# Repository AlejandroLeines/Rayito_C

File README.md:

# Rayito_C
En este repositorio se encuentra el codigo de Rayito en lengiaje C

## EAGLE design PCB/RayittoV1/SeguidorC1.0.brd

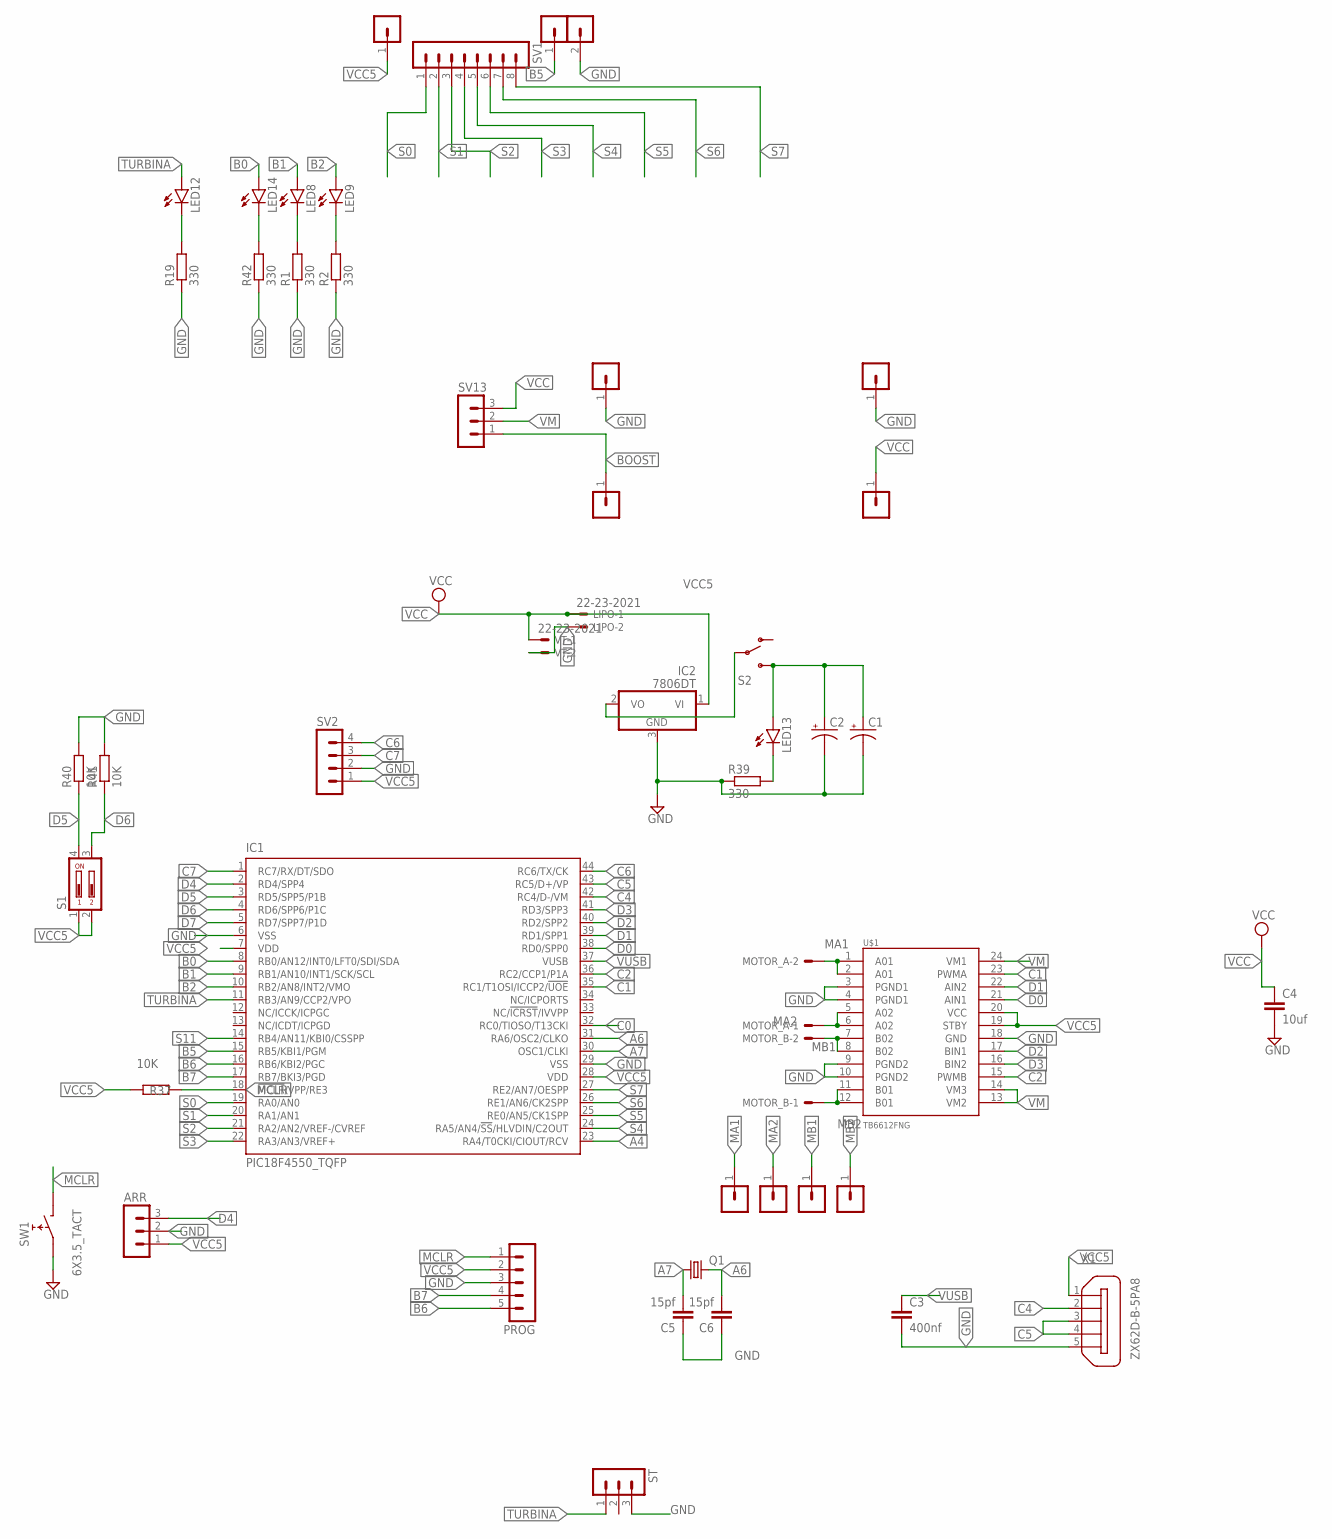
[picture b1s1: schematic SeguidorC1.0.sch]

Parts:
ARR: MA03-1
C1, C2: CPOL-US153CLV-0505; 153CLV-0505
C3: 400nf; C0805
C4: 10uf; C0805
C5, C6: 15pf; C0805
IC1: PIC18F4550_TQFP; TQFP44
IC2: 7806DT; TO252
LED8, LED9, LED12, LED13, LED14: LEDCHIP-LED0805; CHIP-LED0805
LIPO: 22-23-2021
MOTOR_A: 22-23-2021
MOTOR_B: 22-23-2021
PROG: MA05-1
Q1: CRYSTALHC49U-V; HC49U-V
R1, R2, R19, R39, R42: 330; R0805
R37, R40, R41: 10K; R0805
S1: DIP02YL
S2: SWITCH-SPSTPTH; SWITCH-SPDT
ST: MA03-1
SV1: MA08-1
SV2: MA04-1
SV3, SV4, SV5, SV6, SV7, SV9, SV10, SV11, SV12: MA01-1
SV8: MA02-1
SV13: MA03-1
SW1: 6X3.5_TACT; TACT_6X3.5
U$1: TB6612FNG; SSOP24
VT: 22-23-2021
X1: ZX62D-B-5PA8

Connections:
A4: IC1.23 (RA4/T0CKI/CIOUT/RCV)
A6: C6.2, IC1.31 (RA6/OSC2/CLKO), Q1.2
A7: C5.2, IC1.30 (OSC1/CLKI), Q1.1
B0: IC1.8 (RB0/AN12/INT0/LFT0/SDI/SDA), LED14.A
B1: IC1.9 (RB1/AN10/INT1/SCK/SCL), LED8.A
B2: IC1.10 (RB2/AN8/INT2/VMO), LED9.A
B5: IC1.15 (RB5/KBI1/PGM), SV8.1
B6: IC1.16 (RB6/KBI2/PGC), PROG.5
B7: IC1.17 (RB7/BKI3/PGD), PROG.4
BOOST: SV11.1, SV13.1
C0: IC1.32 (RC0/TIOSO/T13CKI)
C1: IC1.35 (RC1/T1OSI/ICCP2/!UOE), U$1.23 (PWMA)
C2: IC1.36 (RC2/CCP1/P1A), U$1.15 (PWMB)
C4: IC1.42 (RC4/D-/VM), X1.2
C5: IC1.43 (RC5/D+/VP), X1.3, X1.4
C6: IC1.44 (RC6/TX/CK), SV2.4
C7: IC1.1 (RC7/RX/DT/SDO), SV2.3
D0: IC1.38 (RD0/SPP0), U$1.21 (AIN1)
D1: IC1.39 (RD1/SPP1), U$1.22 (AIN2)
D2: IC1.40 (RD2/SPP2), U$1.17 (BIN1)
D3: IC1.41 (RD3/SPP3), U$1.16 (BIN2)
D4: ARR.3, IC1.2 (RD4/SPP4)
D5: IC1.3 (RD5/SPP5/P1B), R40.1, S1.4
D6: IC1.4 (RD6/SPP6/P1C), R41.1, S1.3
D7: IC1.5 (RD7/SPP7/P1D)
GND: ARR.2, C1.-, C2.-, C3.2, C4.2, C5.1, C6.1, IC1.6 (VSS), IC1.29 (VSS), IC2.3 (GND), LIPO.2, PROG.3, R1.1, R2.1, R19.1, R39.1, R40.2, R41.2, R42.1, ST.3, SV2.2, SV8.2 (3), SV9.1, SV10.1, SW1.P$1 (1), U$1.3 (PGND1), U$1.4 (PGND1), U$1.9 (PGND2), U$1.10 (PGND2), U$1.18 (GND), VT.2, X1.5
MA1: MOTOR_A.2, SV3.1, U$1.1 (A01), U$1.2 (A01)
MA2: MOTOR_A.1, SV4.1, U$1.5 (A02), U$1.6 (A02)
MB1: MOTOR_B.2, SV5.1, U$1.7 (B02), U$1.8 (B02)
MB2: MOTOR_B.1, SV6.1, U$1.11 (B01), U$1.12 (B01)
MCLR: IC1.18 (!MCLR!/VPP/RE3), PROG.1, R37.2, SW1.P$2 (2)
unnamed: IC2.2 (VO), S2.2
unnamed: LED8.C, R1.2
unnamed: LED9.C, R2.2
unnamed: LED12.C, R19.2
unnamed: LED13.C, R39.2
unnamed: LED14.C, R42.2
S0: IC1.19 (RA0/AN0), SV1.1
S1: IC1.20 (RA1/AN1), SV1.2
S2: IC1.21 (RA2/AN2/VREF-/CVREF), SV1.3
S3: IC1.22 (RA3/AN3/VREF+), SV1.4
S4: IC1.24 (RA5/AN4/!SS!/HLVDIN/C2OUT), SV1.5
S5: IC1.25 (RE0/AN5/CK1SPP), SV1.6
S6: IC1.26 (RE1/AN6/CK2SPP), SV1.7
S7: IC1.27 (RE2/AN7/OESPP), SV1.8
S11: IC1.14 (RB4/AN11/KBI0/CSSPP)
TURBINA: IC1.11 (RB3/AN9/CCP2/VPO), LED12.A, ST.1
VCC: C4.1, IC2.1 (VI), LIPO.1, SV12.1, SV13.3, VT.1
VCC5: ARR.1, C1.+, C2.+, IC1.7 (VDD), IC1.28 (VDD), LED13.A, PROG.2, R37.1, S1.1, S1.2, S2.3 (S), SV2.1, SV7.1, U$1.19 (STBY), U$1.20 (VCC), X1.1
VM: SV13.2, U$1.13 (VM2), U$1.14 (VM3), U$1.24 (VM1)
VUSB: C3.1, IC1.37 (VUSB)

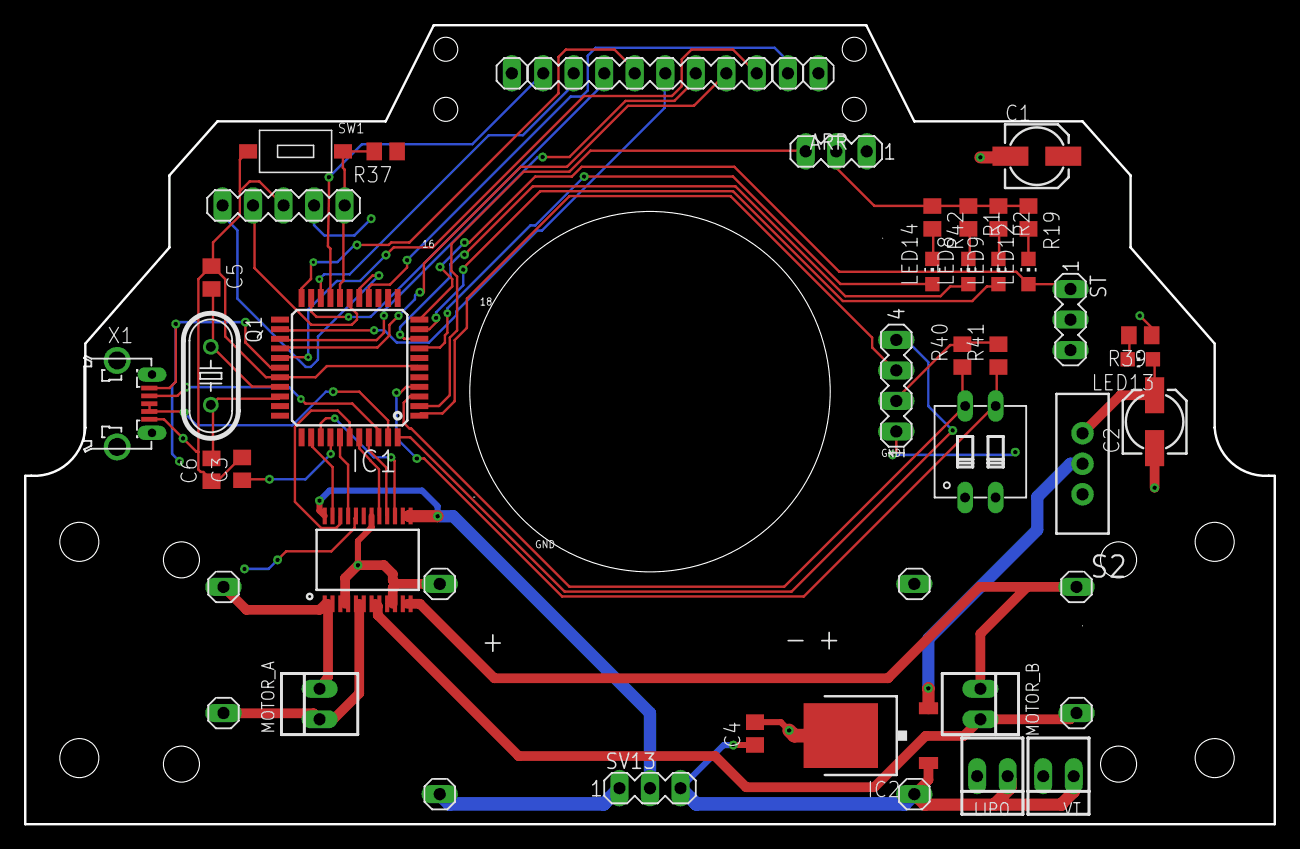
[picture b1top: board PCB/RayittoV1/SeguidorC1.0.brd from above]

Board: 2 copper layers, 104.0 x 66.5 mm, 47 parts (0 on the bottom side), 47 nets.

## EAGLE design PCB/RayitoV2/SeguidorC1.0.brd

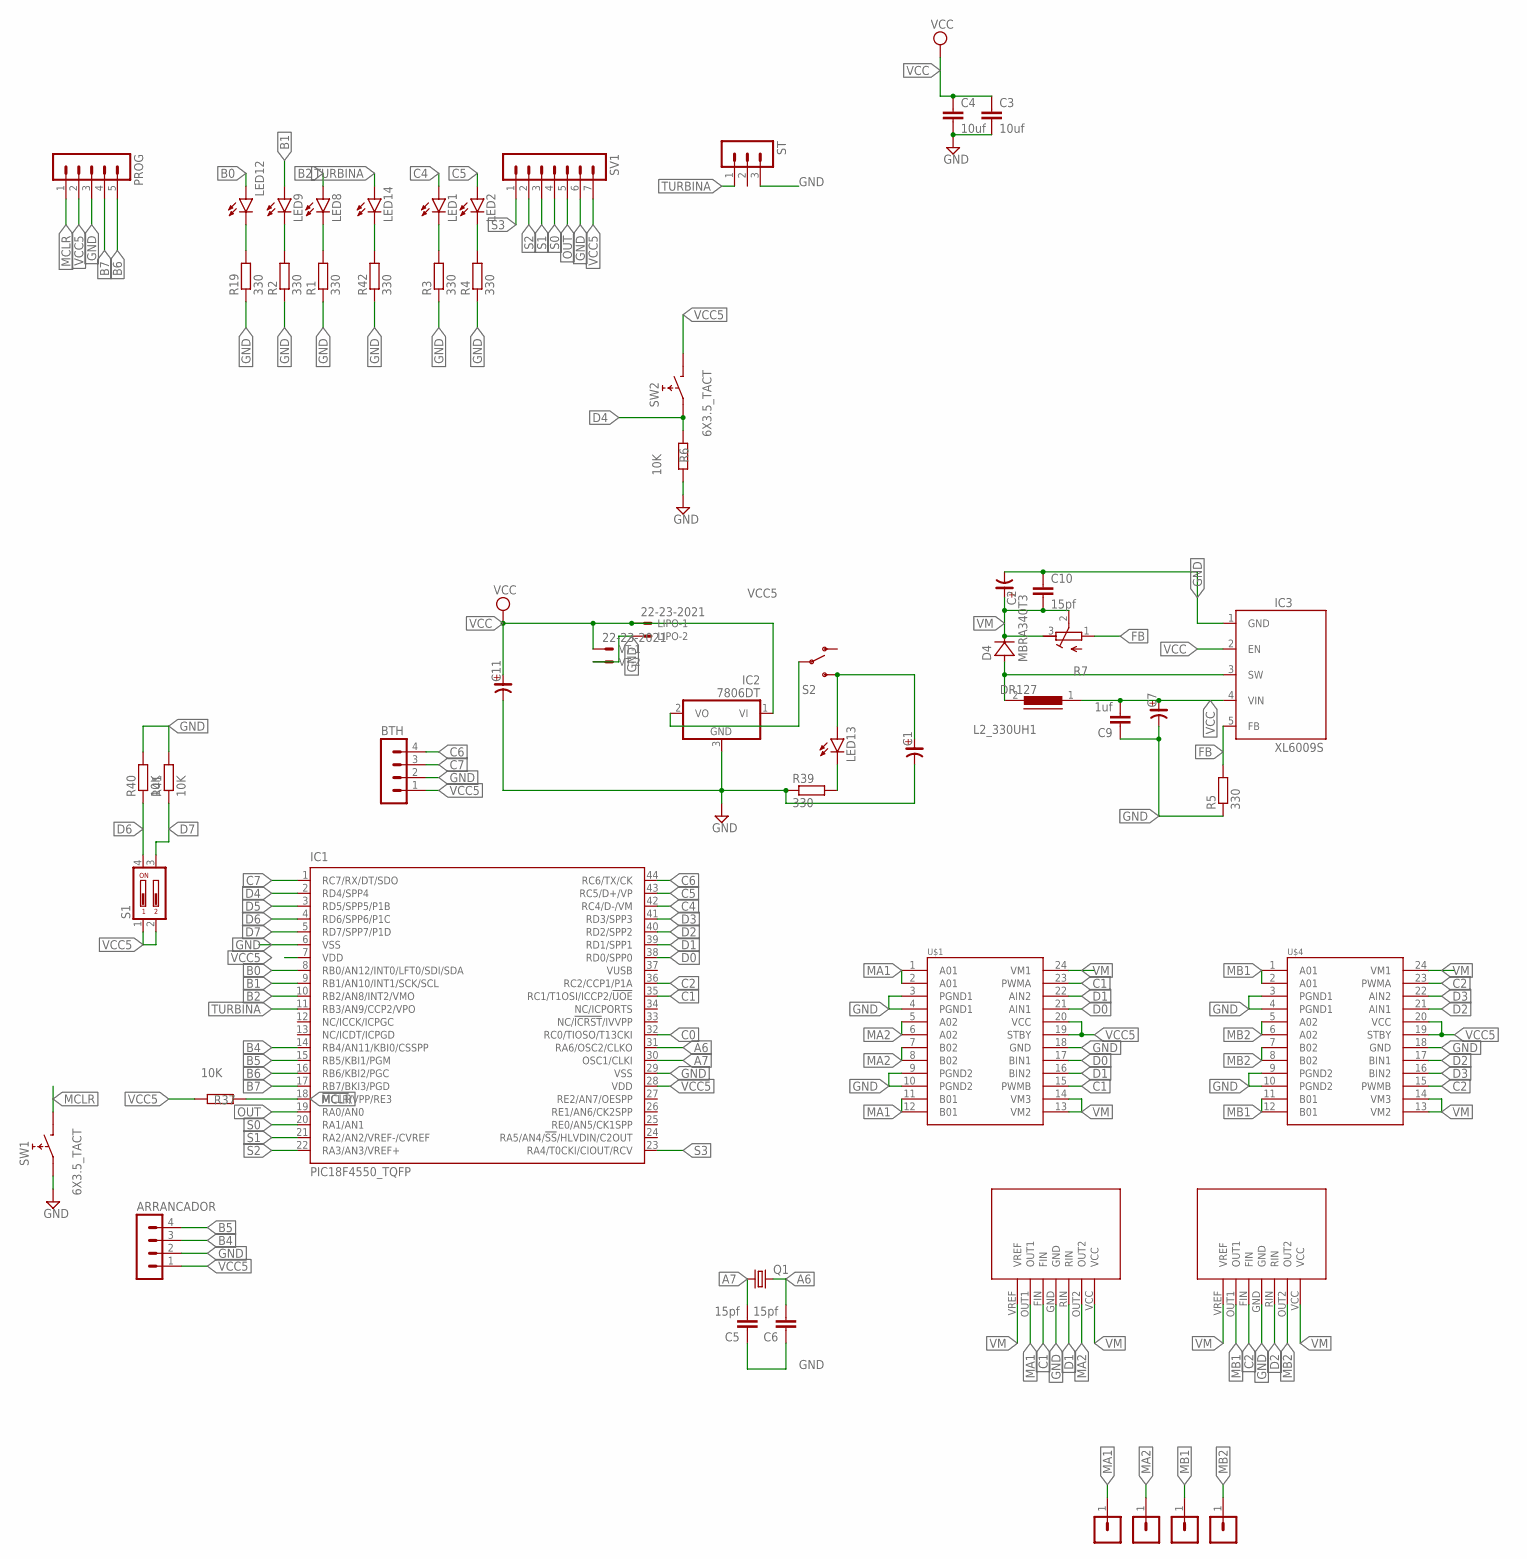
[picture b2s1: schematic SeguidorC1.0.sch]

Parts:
ARRANCADOR: MA04-1
BTH: MA04-1
C1, C2, C7, C11: CP_SV-D; CSV-D
C3, C4: 10uf; C0805
C5, C6, C10: 15pf; C0805
C9: 1uf; C0805
D4: MBRA340T3; SMA
IC1: PIC18F4550_TQFP; TQFP44
IC2: 7806DT; TO252
IC3: XL6009S; TO263-5
L2_330UH1: DR127
LED1, LED2, LED8, LED9, LED12, LED13, LED14: LEDCHIP-LED0805; CHIP-LED0805
LIPO: 22-23-2021
PROG: MA05-1
Q1: CRYSTALHC49U-V; HC49U-V
R1, R2, R3, R4, R5, R19, R39, R42: 330; R0805
R6, R37, R40, R41: 10K; R0805W
R7: R-TRIMM3296W; RTRIM3296W
S1: DIP02YL
S2: SWITCH-SPSTPTH; SWITCH-SPDT
ST: MA03-1
SV1: MA07-1
SV3, SV4, SV5, SV6: MA01-1
SW1, SW2: 6X3.5_TACT; TACT_6X3.5
U$1, U$4: TB6621FNG; SSOP24
U$2, U$3: BD623XXX; HRP7
VT: 22-23-2021

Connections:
A6: C6.2, IC1.31 (RA6/OSC2/CLKO), Q1.2
A7: C5.2, IC1.30 (OSC1/CLKI), Q1.1
B0: IC1.8 (RB0/AN12/INT0/LFT0/SDI/SDA), LED12.A
B1: IC1.9 (RB1/AN10/INT1/SCK/SCL), LED9.A
B2: IC1.10 (RB2/AN8/INT2/VMO), LED8.A
B4: ARRANCADOR.3, IC1.14 (RB4/AN11/KBI0/CSSPP)
B5: ARRANCADOR.4, IC1.15 (RB5/KBI1/PGM)
B6: IC1.16 (RB6/KBI2/PGC), PROG.5
B7: IC1.17 (RB7/BKI3/PGD), PROG.4
C0: IC1.32 (RC0/TIOSO/T13CKI)
C1: IC1.35 (RC1/T1OSI/ICCP2/!UOE), U$1.15 (PWMB), U$1.23 (PWMA), U$2.FIN
C2: IC1.36 (RC2/CCP1/P1A), U$3.FIN, U$4.15 (PWMB), U$4.23 (PWMA)
C4: IC1.42 (RC4/D-/VM), LED1.A
C5: IC1.43 (RC5/D+/VP), LED2.A
C6: BTH.4, IC1.44 (RC6/TX/CK)
C7: BTH.3, IC1.1 (RC7/RX/DT/SDO)
D0: IC1.38 (RD0/SPP0), U$1.17 (BIN1), U$1.21 (AIN1)
D1: IC1.39 (RD1/SPP1), U$1.16 (BIN2), U$1.22 (AIN2), U$2.RIN
D2: IC1.40 (RD2/SPP2), U$3.RIN, U$4.17 (BIN1), U$4.21 (AIN1)
D3: IC1.41 (RD3/SPP3), U$4.16 (BIN2), U$4.22 (AIN2)
D4: IC1.2 (RD4/SPP4), R6.2, SW2.P$1 (1)
D5: IC1.3 (RD5/SPP5/P1B)
D6: IC1.4 (RD6/SPP6/P1C), R40.1, S1.4
D7: IC1.5 (RD7/SPP7/P1D), R41.1, S1.3
FB: IC3.5 (FB), R5.2, R7.1 (A)
GND: ARRANCADOR.2, BTH.2, C1.-, C2.-, C3.2, C4.2, C5.1, C6.1, C7.-, C9.1, C10.1, C11.-, IC1.6 (VSS), IC1.29 (VSS), IC2.3 (GND), IC3.1 (GND), LIPO.2, PROG.3, R1.1, R2.1, R3.1, R4.1, R5.1, R6.1, R19.1, R39.1, R40.2, R41.2, R42.1, ST.3, SV1.6, SW1.P$1 (1), U$1.3 (PGND1), U$1.4 (PGND1), U$1.9 (PGND2), U$1.10 (PGND2), U$1.18 (GND), U$2.GND, U$3.GND, U$4.3 (PGND1), U$4.4 (PGND1), U$4.9 (PGND2), U$4.10 (PGND2), U$4.18 (GND), VT.2
MA1: SV3.1, U$1.1 (A01), U$1.2 (A01), U$1.11 (B01), U$1.12 (B01), U$2.OUT1
MA2: SV4.1, U$1.5 (A02), U$1.6 (A02), U$1.7 (B02), U$1.8 (B02), U$2.OUT2
MB1: SV5.1, U$3.OUT1, U$4.1 (A01), U$4.2 (A01), U$4.11 (B01), U$4.12 (B01)
MB2: SV6.1, U$3.OUT2, U$4.5 (A02), U$4.6 (A02), U$4.7 (B02), U$4.8 (B02)
MCLR: IC1.18 (!MCLR!/VPP/RE3), PROG.1, R37.2, SW1.P$2 (2)
unnamed: IC2.2 (VO), S2.2
unnamed: LED8.C, R1.2
unnamed: LED9.C, R2.2
unnamed: LED1.C, R3.2
unnamed: LED2.C, R4.2
unnamed: D4.A, IC3.3 (SW), L2_330UH1.2
unnamed: LED12.C, R19.2
unnamed: LED13.C, R39.2
unnamed: LED14.C, R42.2
OUT: IC1.19 (RA0/AN0), SV1.5
S0: IC1.20 (RA1/AN1), SV1.4
S1: IC1.21 (RA2/AN2/VREF-/CVREF), SV1.3
S2: IC1.22 (RA3/AN3/VREF+), SV1.2
S3: IC1.23 (RA4/T0CKI/CIOUT/RCV), SV1.1
TURBINA: IC1.11 (RB3/AN9/CCP2/VPO), LED14.A, ST.1
VCC: C3.1, C4.1, C7.+, C9.2, C11.+, IC2.1 (VI), IC3.2 (EN), IC3.4 (VIN), L2_330UH1.1, LIPO.1, VT.1
VCC5: ARRANCADOR.1, BTH.1, C1.+, IC1.7 (VDD), IC1.28 (VDD), LED13.A, PROG.2, R37.1, S1.1, S1.2, S2.3 (S), SV1.7, SW2.P$2 (2), U$1.19 (STBY), U$1.20 (VCC), U$4.19 (STBY), U$4.20 (VCC)
VM: C2.+, C10.2, D4.C, R7.2 (S), R7.3 (E), U$1.13 (VM2), U$1.14 (VM3), U$1.24 (VM1), U$2.VCC, U$2.VREF, U$3.VCC, U$3.VREF, U$4.13 (VM2), U$4.14 (VM3), U$4.24 (VM1)

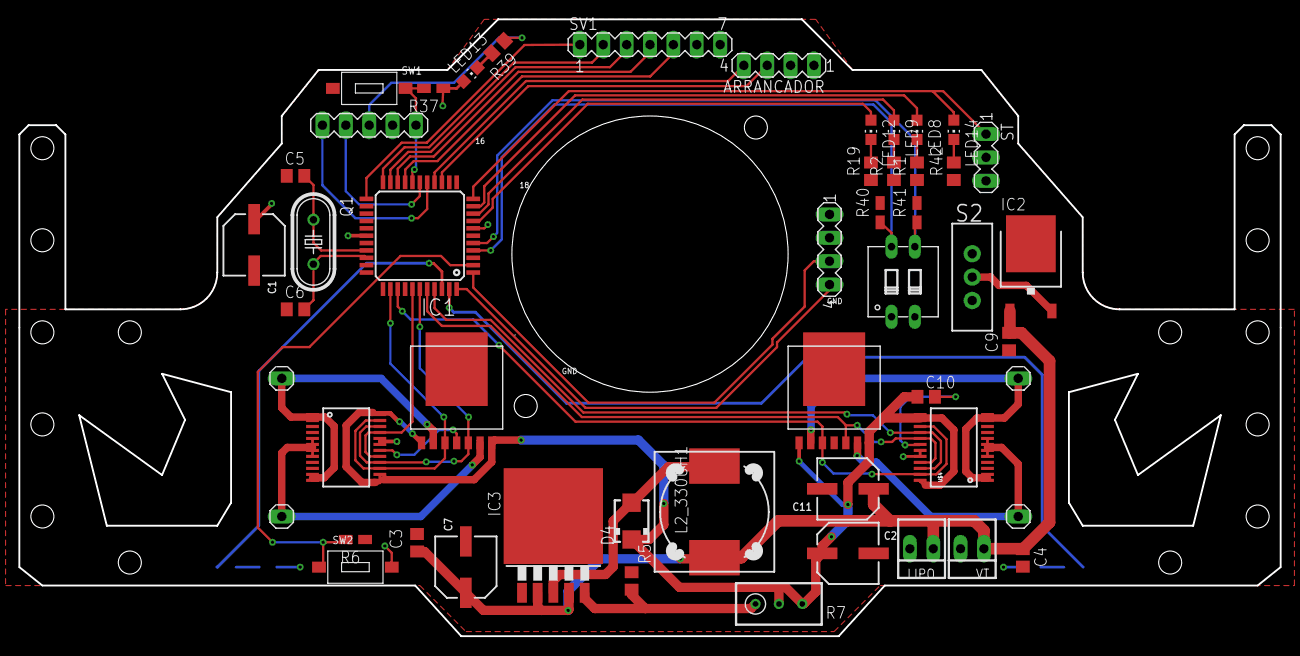
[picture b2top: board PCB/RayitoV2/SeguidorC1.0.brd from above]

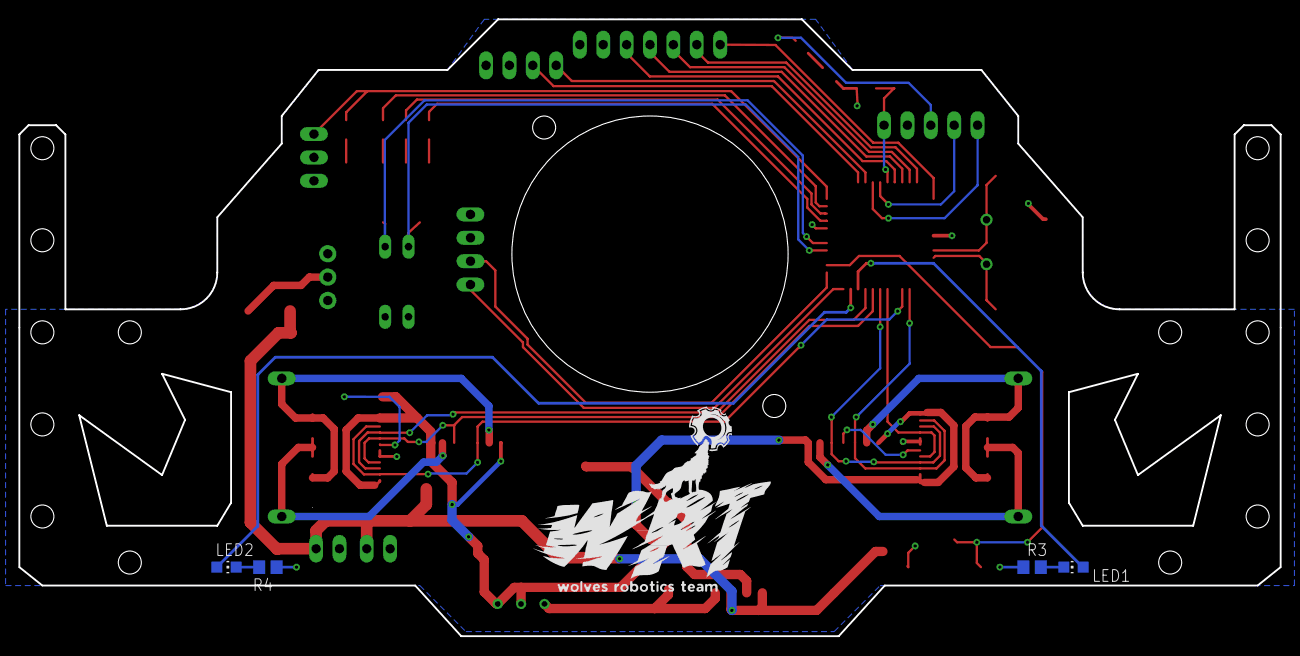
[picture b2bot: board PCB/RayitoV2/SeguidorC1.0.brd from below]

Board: 2 copper layers, 137.0 x 67.0 mm, 55 parts (4 on the bottom side), 47 nets.

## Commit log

2022-04-06 Add files via upload
    archivos principales del robot rayito version C

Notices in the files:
parts and their libraries:
SparkFun: Licensing: CC v3.0 Share-Alike You are welcome to use this library for commercial purposes.
rc-master-smd: Copyright (C) 2007, Bob Starr
SparkFun-IC-Special-Function: Licensing: Creative Commons ShareAlike 4.0 International - https://creativecommons.org/licenses/by-sa/4.0
